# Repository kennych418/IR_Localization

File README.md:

# IR_Localization

This folder contains hardware and software for our ECE202A project on IR localization.

### [Project Website](https://kennych418.github.io/)

### [Project Website (Repo)](https://github.com/kennych418/kennych418.github.io)

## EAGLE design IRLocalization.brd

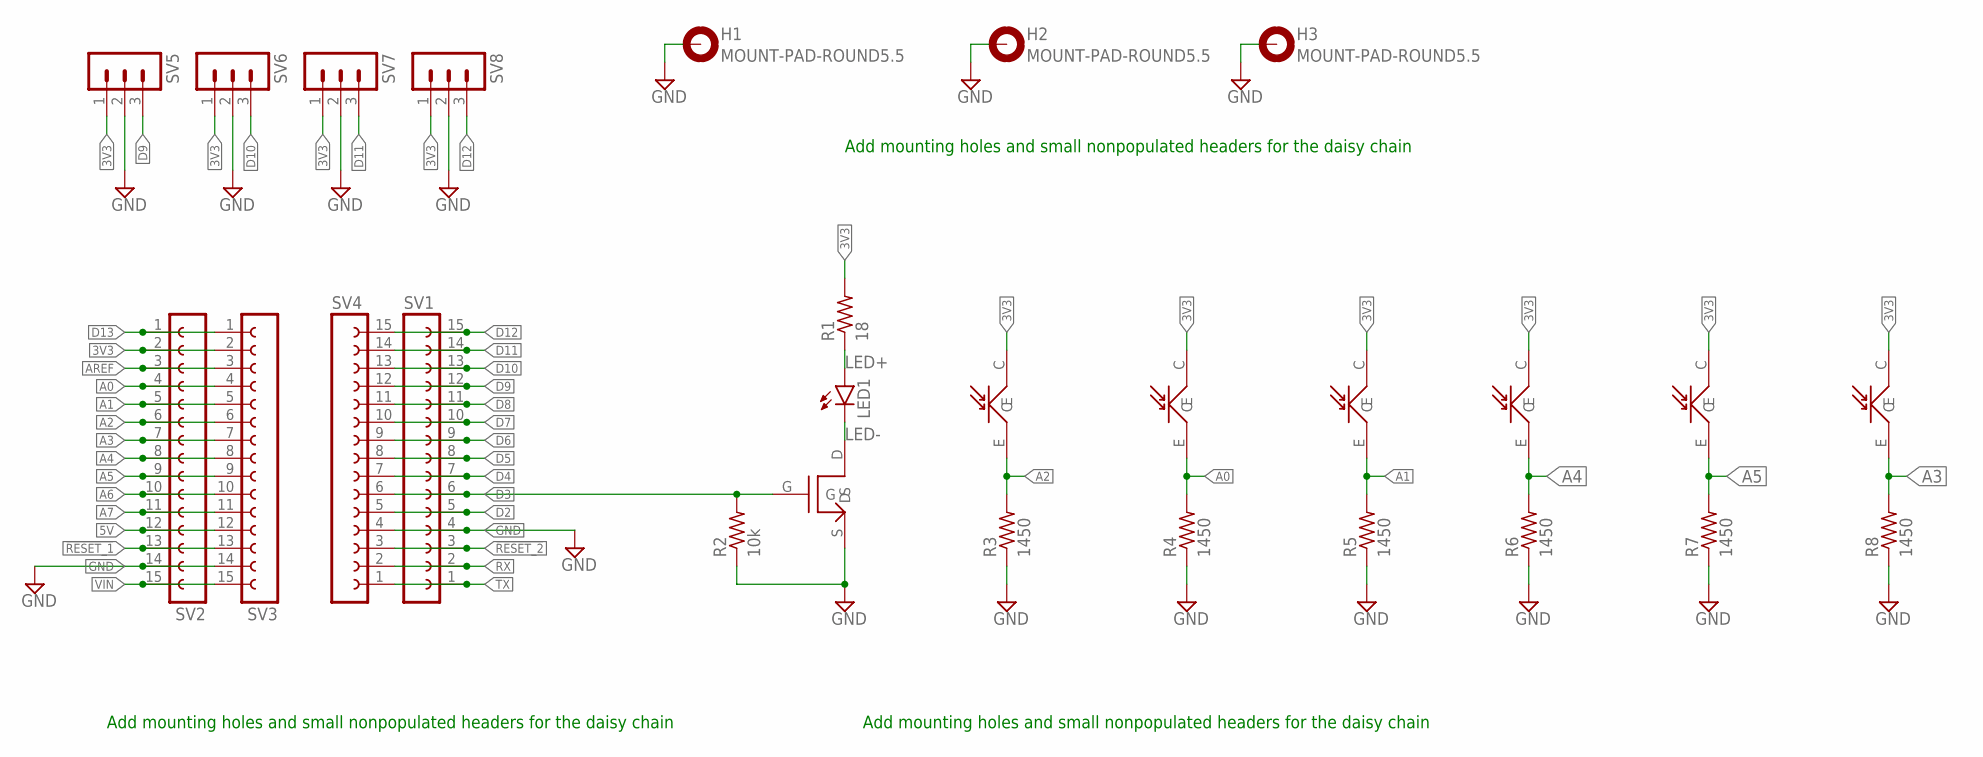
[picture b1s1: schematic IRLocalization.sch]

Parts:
H1, H2, H3: MOUNT-PAD-ROUND5.5; 5,5-PAD
LED1: LED5MM
R1: 18; R0603
R2: 10k; R0603
R3, R4, R5, R6, R7, R8: 1450; R0603
SV1, SV2, SV3, SV4: FE15-1; FE15
SV5, SV6, SV7, SV8: MA03-1
U$1: NMOS_SOT23; SOT23
U$2, U$3, U$4, U$5, U$6, U$7: PHOTOTRANSISTOR_2.54; 2.54_TH

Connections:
3V3: R1.2, SV2.2, SV3.2, SV5.1, SV6.1, SV7.1, SV8.1, U$2.C, U$3.C, U$4.C, U$5.C, U$6.C, U$7.C
5V: SV2.12, SV3.12
!RESET_1: SV2.13, SV3.13
!RESET_2: SV1.3, SV4.3
A0: R4.2, SV2.4, SV3.4, U$3.E
A1: R5.2, SV2.5, SV3.5, U$4.E
A2: R3.2, SV2.6, SV3.6, U$2.E
A3: R8.2, SV2.7, SV3.7, U$7.E
A4: R6.2, SV2.8, SV3.8, U$5.E
A5: R7.2, SV2.9, SV3.9, U$6.E
A6: SV2.10, SV3.10
A7: SV2.11, SV3.11
AREF: SV2.3, SV3.3
D2: SV1.5, SV4.5
D3: R2.2, SV1.6, SV4.6, U$1.G
D4: SV1.7, SV4.7
D5: SV1.8, SV4.8
D6: SV1.9, SV4.9
D7: SV1.10, SV4.10
D8: SV1.11, SV4.11
D9: SV1.12, SV4.12, SV5.3
D10: SV1.13, SV4.13, SV6.3
D11: SV1.14, SV4.14, SV7.3
D12: SV1.15, SV4.15, SV8.3
D13: SV2.1, SV3.1
GND: H1.B5,5, H2.B5,5, H3.B5,5, R2.1, R3.1, R4.1, R5.1, R6.1, R7.1, R8.1, SV1.4, SV2.14, SV3.14, SV4.4, SV5.2, SV6.2, SV7.2, SV8.2, U$1.S
LED+: LED1.A, R1.1
LED-: LED1.K (C), U$1.D
RX: SV1.2, SV4.2
TX: SV1.1, SV4.1
VIN: SV2.15, SV3.15

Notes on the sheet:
Add mounting holes and small nonpopulated headers for the daisy chain

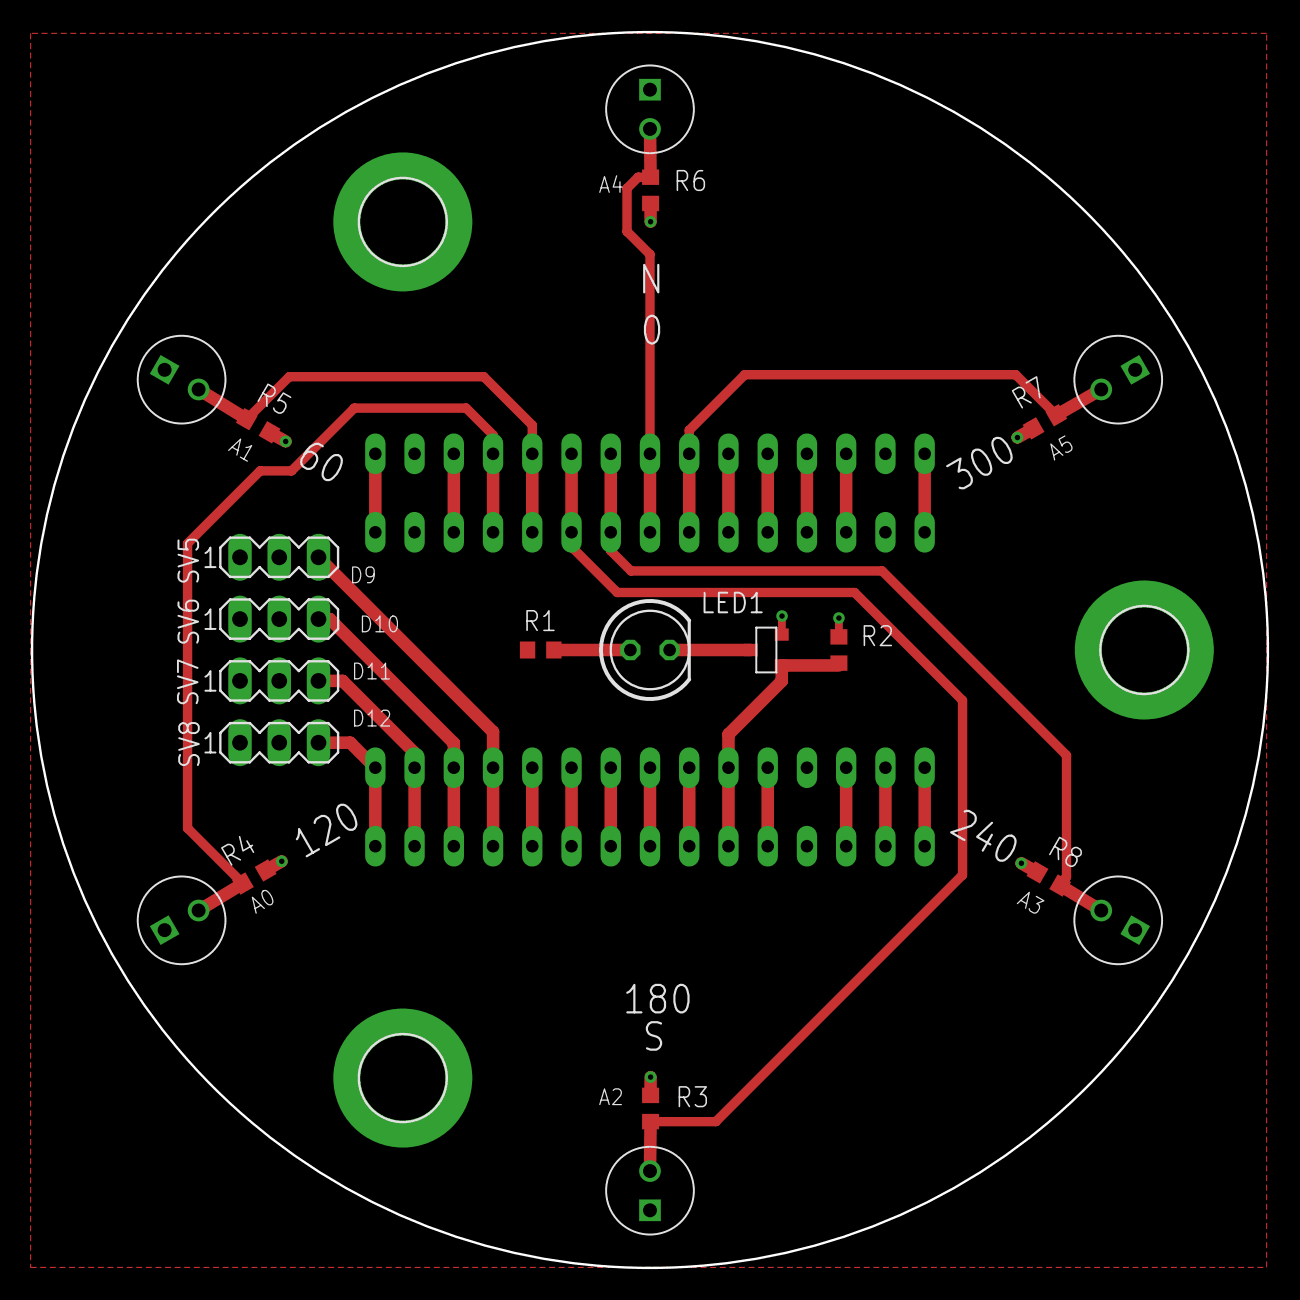
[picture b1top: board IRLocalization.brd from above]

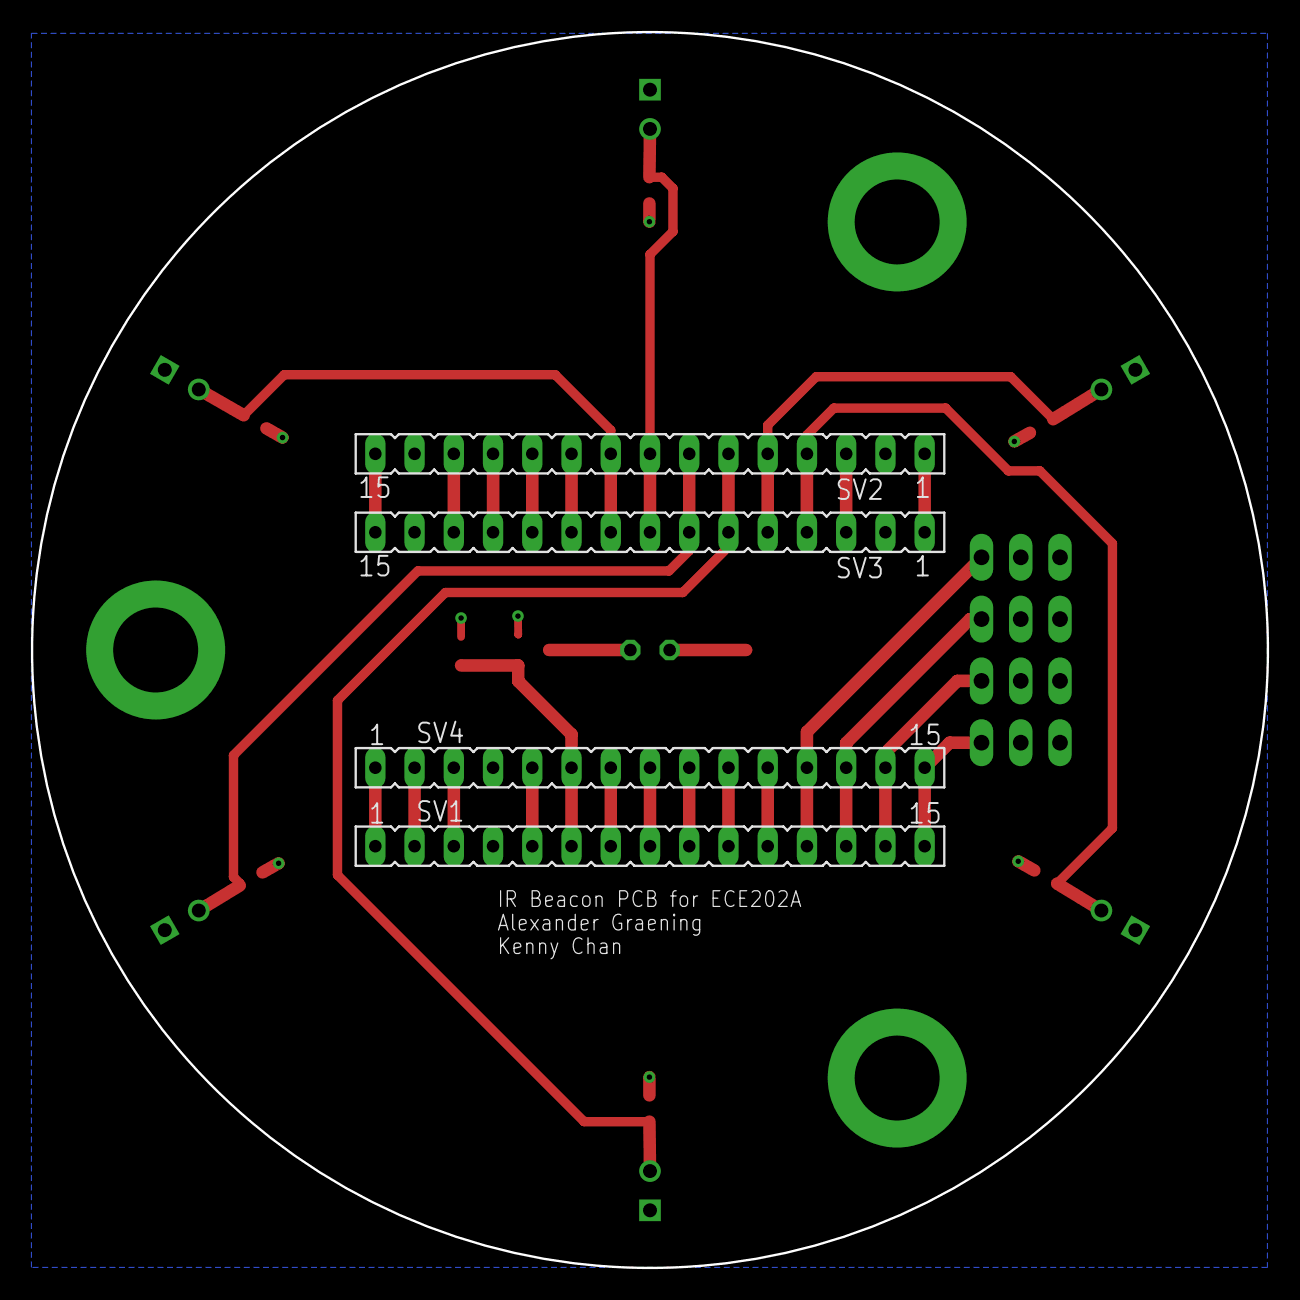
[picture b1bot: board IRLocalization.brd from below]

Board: 2 copper layers, 80.0 x 80.0 mm, 27 parts (4 on the bottom side), 31 nets.

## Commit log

2020-10-23 Blank project and schematic
2020-11-03 First Draft Schematic and Part Library
2020-11-03 Added notes
2020-11-07 PCB added
2020-11-07 Adding barebones BLE code
2020-11-07 Added mounting holes
2020-11-09 Fixed orientation for nano headers
2020-11-09 Added silkscreen to top and bottom of the board.
2020-11-11 Added frame CAD files
2020-11-11 Included IR Emitter Height
2020-11-11 Added IMU files
2020-11-11 Code edit
2020-11-17 Some updates to the IMU code
2020-11-17 Added main code frame
2020-11-25 Adding data
2020-11-25 Added IR test code
2020-11-25 fixed bug with distance function in the ir_test code
2020-11-25 Random start, can connect but crashes
2020-12-07 Before big adjustments 12/06
2020-12-07 Consistent connection with ID, Enable, Time, Dist
2020-12-07 Services added
2020-12-08 Before switching central and peripheral
2020-12-08 My hopes are crushed and soul is destroyed, but at least two nodes can talk to each other
2020-12-13 Adding connectionless BLE code
2020-12-15 Added only broadcast version with compass and receiver streams
2020-12-16 Added preliminary version of code with handshaking algorithm
2020-12-17 Intermediate version
2020-12-17 Adding visualizer
2020-12-17 Nearly complete with a few bugs
2020-12-19 Adding files as backup before changing to use tensorflow lite model
2020-12-19 added .ipynb with neural net code
